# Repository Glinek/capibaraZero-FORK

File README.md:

# CapibaraZero FORK
This repo contains PCBs designed by me for [the capibara zero](https://capibarazero.com/). 

### Gerber files are located under /KiCad/fabrication files for PCB

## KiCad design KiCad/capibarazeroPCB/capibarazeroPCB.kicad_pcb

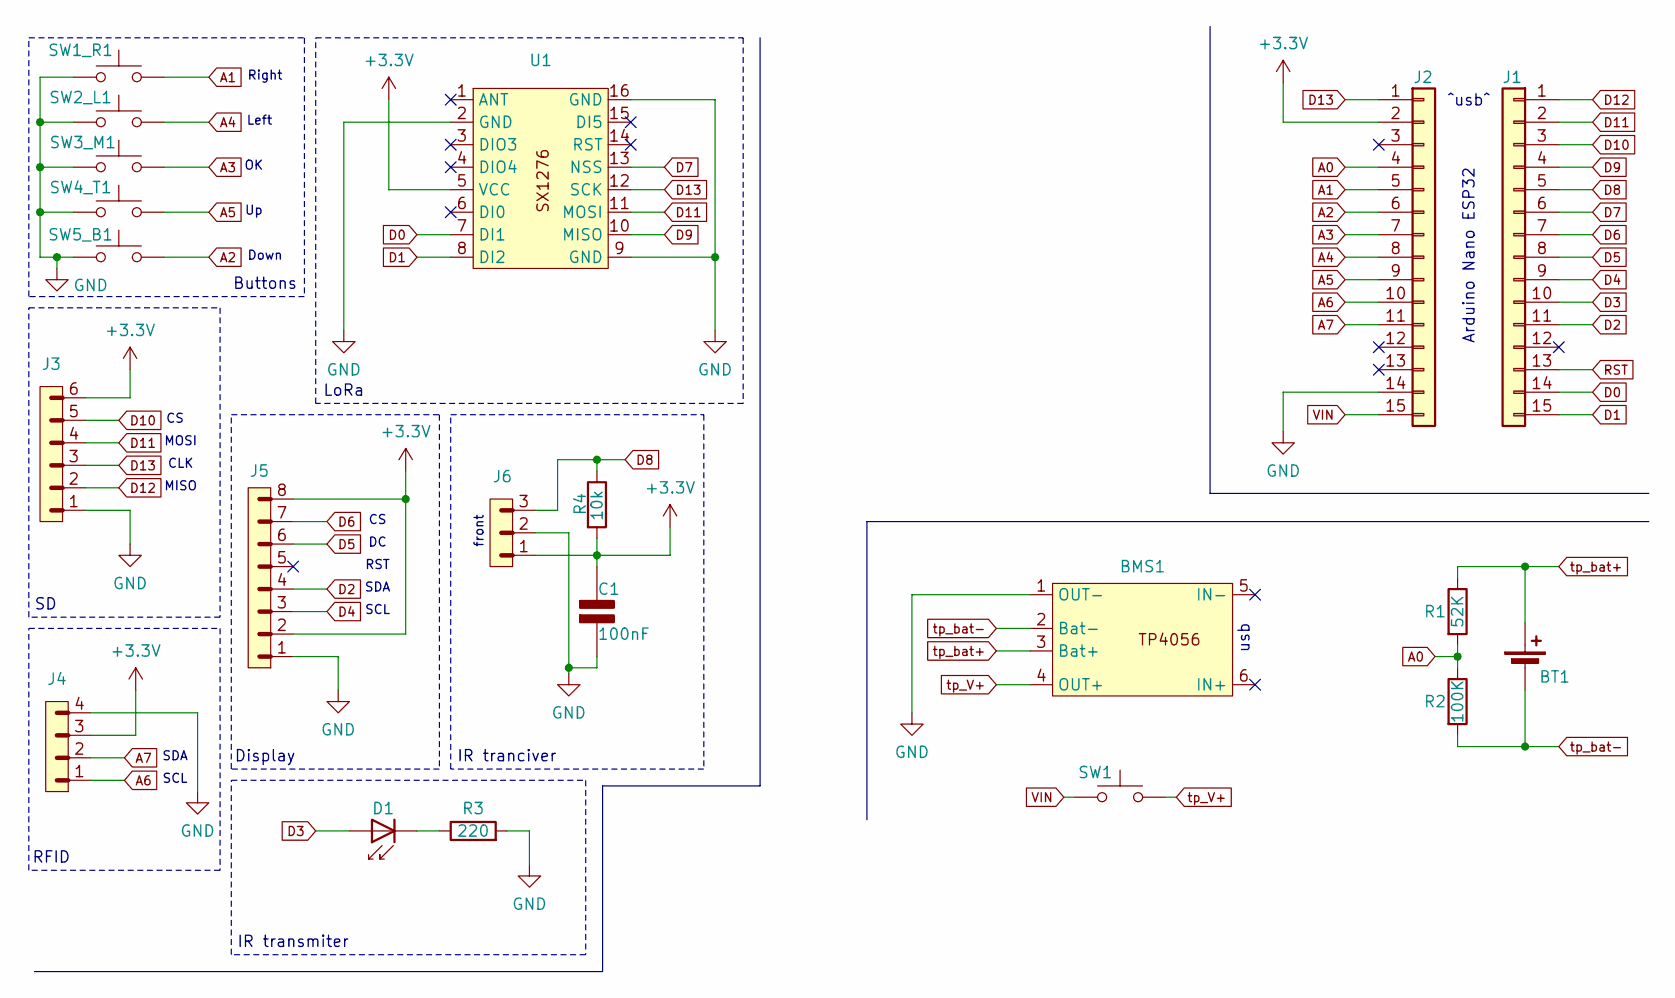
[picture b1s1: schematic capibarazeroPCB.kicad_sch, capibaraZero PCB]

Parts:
BMS1: tp4056_v2
BT1: Battery_Cell; BatteryHolder_Keystone_1042_1x18650
C1: 100nF; C_0603_1608Metric_Pad1.08x0.95mm_HandSolder; Rating V
D1: IR204A; LED_D3.0mm_IRBlack
J1, J2: Conn_01x15; PinHeader_1x15_P2.54mm_Vertical
J3: PINHD_1x6_Male; smd_connectorGeneric_1x6-2.54mm
J4: PINHD_1x4_Male; smd_connecorGeneric_1x4-2.54mm
J5: PINHD_1x8_Male; PinHeader_1x08_P2.54mm_Vertical
J6: PINHD_1x3_Male; PinHeader_1x03_P2.54mm_Vertical
R1: 52K; R_1206_3216Metric_Pad1.30x1.75mm_HandSolder
R2: 100K; R_1206_3216Metric_Pad1.30x1.75mm_HandSolder
R3: 220; R_1206_3216Metric_Pad1.30x1.75mm_HandSolder
R4: 10k; R_1206_3216Metric_Pad1.30x1.75mm_HandSolder
SW1: SW_Push; switch
SW1_R1, SW2_L1, SW3_M1, SW4_T1, SW5_B1: SW_Push; SW_PUSH_6mm
U1: sx1276LoRa

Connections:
+3.3V: C1.1 (+), J2.2, J3.6, J4.3, J5.2, J5.8, J6.1, R4.2, U1.5 (VCC)
A0: J2.4, R1.2, R2.1
A1: J2.5, SW1_R1.2
A2: J2.6, SW5_B1.2
A3: J2.7, SW3_M1.2
A4: J2.8, SW2_L1.2
A5: J2.9, SW4_T1.2
A6: J2.10, J4.1
A7: J2.11, J4.2
D0: J1.14, U1.7 (DI1)
D1: J1.15, U1.8 (DI2)
D2: J1.11, J5.4
D3: D1.2 (A), J1.10
D4: J1.9, J5.3
D5: J1.8, J5.6
D6: J1.7, J5.7
D7: J1.6, U1.13 (NSS)
D8: J1.5, J6.3, R4.1
D9: J1.4, U1.10 (MISO)
D10: J1.3, J3.5
D11: J1.2, J3.4, U1.11 (MOSI)
D12: J1.1, J3.2
D13: J2.1, J3.3, U1.12 (SCK)
GND: BMS1.1 (OUT-), C1.2 (-), J2.14, J3.1, J4.4, J5.1, J6.2, R3.2, SW1_R1.1, SW2_L1.1, SW3_M1.1, SW4_T1.1, SW5_B1.1, U1.2 (GND), U1.9 (GND), U1.16 (GND)
unnamed: D1.1 (K), R3.1
RST: J1.13
VIN: J2.15, SW1.1
tp_V+: BMS1.4 (OUT+), SW1.2
tp_bat+: BMS1.3 (Bat+), BT1.1 (+), R1.1
tp_bat-: BMS1.2 (Bat-), BT1.2 (-), R2.2

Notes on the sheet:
SCL
Down
Buttons
Right
Arduino Nano ESP32
IR transmiter
usb
RST
CLK
front
RFID
^usb^
LoRa
Display
SDA
MOSI
SDA
Left
IR tranciver
MISO

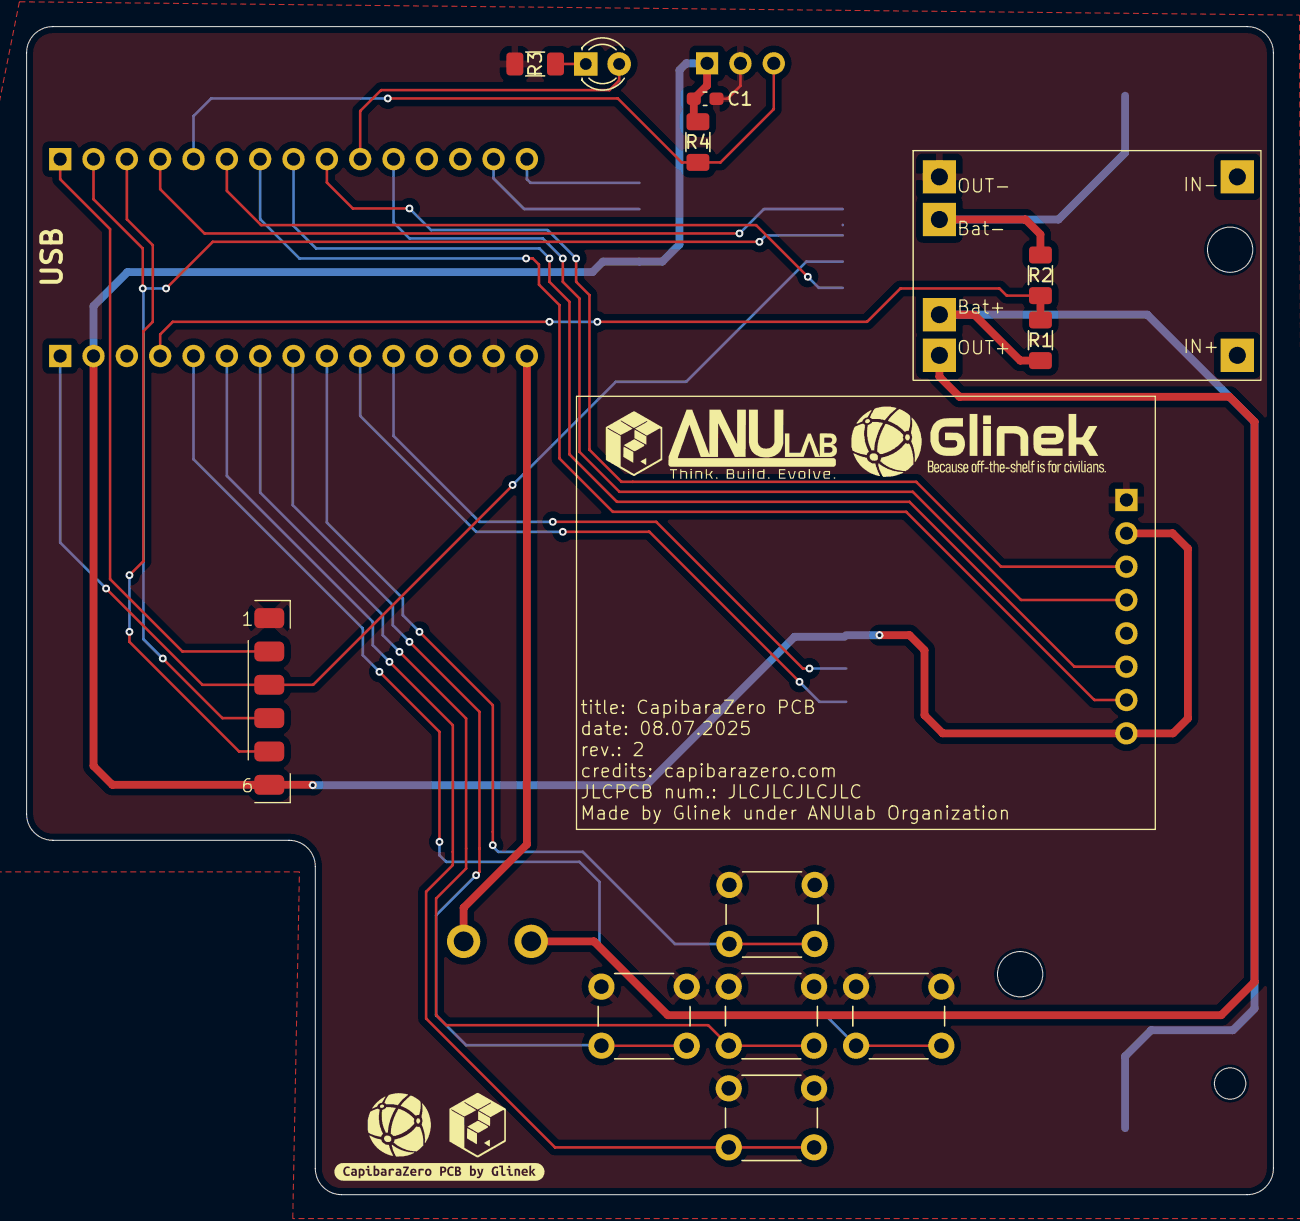
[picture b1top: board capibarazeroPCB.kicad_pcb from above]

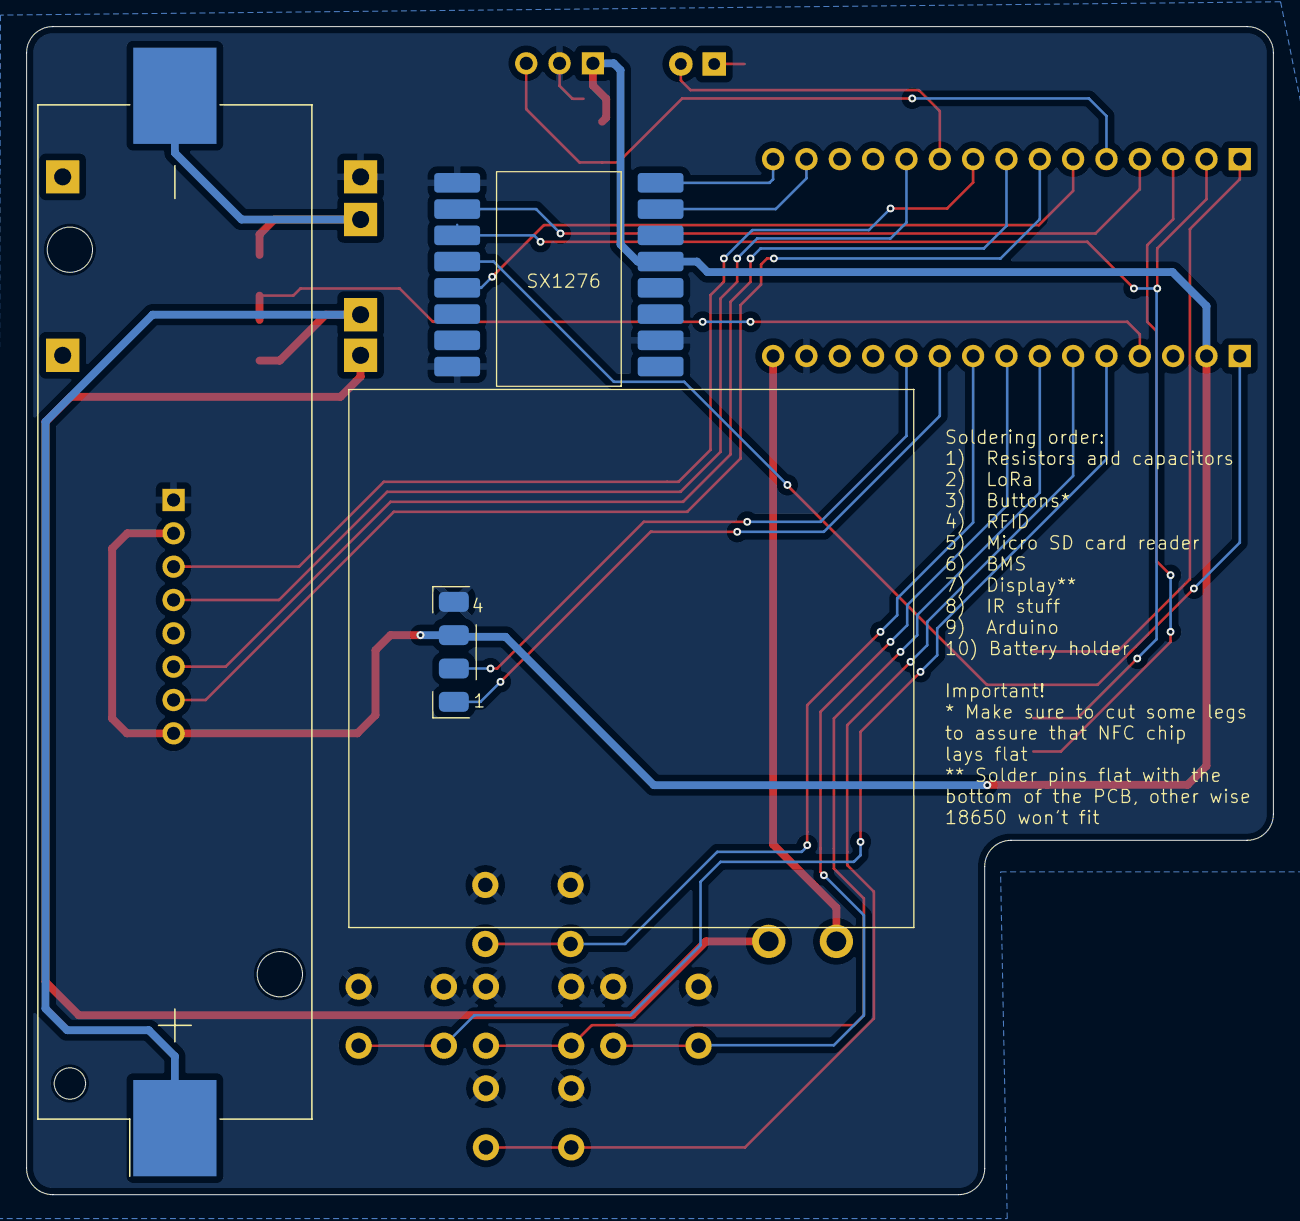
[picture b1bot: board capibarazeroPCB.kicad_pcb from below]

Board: 2 copper layers, 95.0 x 89.0 mm, 22 parts (3 on the bottom side), 29 nets.

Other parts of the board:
kibuzzard-686CF35A: G***; kibuzzard-686CF35A

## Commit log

2025-06-17 model update
2025-06-26 case finished
2025-07-08 pcb update to rev2 - 08.07.2025
2025-11-09 minor update
2025-11-10 readme update
